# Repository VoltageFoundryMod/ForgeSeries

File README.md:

<div align="center">

# ForgeSeries

**One open-source Eurorack platform. Many modules. You choose which one it is at
power-on — and the same firmware also runs inside VCV Rack.**

[The modules](#the-modules) ·
[Get one running](#get-one-running) ·
[The board](#the-board) ·
[Building from source](#building) ·
[How it fits together](#how-it-fits-together)

[Website & manuals](https://vfmod.com) ·
[Hardware repo](https://github.com/VoltageFoundryMod/ForgeSeries-Hardware) ·
[Firmware releases](https://github.com/VoltageFoundryMod/ForgeSeries/releases) ·
[Support on Patreon](https://patreon.com/carlosedp)

</div>

---

## What this is

ForgeSeries is a family of 6HP Eurorack modules from **Voltage Foundry Modular**
that all share a single board: a Seeed XIAO RP2040, a 128×64 OLED, one encoder,
3 CV inputs and 4 outputs. What makes the board a clock generator or a quantizer
is nothing but firmware.

This repository holds all of it:

- **The firmware** — one image (`src/`) that contains _every_ module. Hold
  the encoder at power-on to pick which one boots; the choice persists.
- **The VCV Rack plugin** — not a reimplementation. The actual firmware runs
  inside Rack against a hardware shim, with the OLED emulated pixel for pixel,
  so a patch behaves the same on the metal and on the screen.
- **The shared core** — board bring-up, CV calibration, storage, display and
  menu plumbing that every module builds on.

Schematics, PCB and panel files are open too, in the separate
[ForgeSeries-Hardware](https://github.com/VoltageFoundryMod/ForgeSeries-Hardware)
repository.

## The modules

|                                                                                 | Module                                    | What it does                                                                                                                                                                                                      | Docs                                                                                                                                                                                      |
| ------------------------------------------------------------------------------- | ----------------------------------------- | ----------------------------------------------------------------------------------------------------------------------------------------------------------------------------------------------------------------- | ----------------------------------------------------------------------------------------------------------------------------------------------------------------------------------------- |
|    | **ClockForge**<br><sub>`apps/clk`</sub>   | Clock generator and modulation source. Four outputs with individual multiply/divide, waveforms, envelopes, Euclidean rhythms, swing, phase, probability, cross-operations and loops. Tap tempo and external sync. | [Overview](apps/clk/Readme.md) · [Manual](apps/clk/Manual.md) · [VCV port](apps/clk/docs/VCVRack_Plugin.md) · [ModularGrid](https://modulargrid.net/e/voltage-foundry-modular-clockforge) |
|      | **NoteForge**<br><sub>`apps/dq`</sub>     | Dual quantizer. Two independent channels, each with its own editable 12-note scale mask, octave shift, glide, sample & hold and a gate/envelope output.                                                           | [Overview](apps/dq/Readme.md) · [Manual](apps/dq/Manual.md) · [VCV port](apps/dq/docs/VCVRack_Plugin.md) · [ModularGrid](https://modulargrid.net/e/voltage-foundry-modular-noteforge)     |
|  | **GravityForge**<br><sub>`apps/gen`</sub> | Physics-based generative sequencer. Balls fall inside two rotating containers and ring scale-tuned pegs; a proximity control slides the two from independent sequencers into one entangled instrument.            | [Overview](apps/gen/Readme.md) · [Manual](apps/gen/Manual.md) · [Design notes](apps/gen/docs/Design.md) · [ModularGrid](https://modulargrid.net/e/voltage-foundry-modular-gravityforge)   |
|     | **ForgeView**<br><sub>`apps/scp`</sub>    | Oscilloscope and analysis. Dual-trace and single-trace scope, triggered capture, spectrum analyzer, X-Y display and a tuner — with buffered pass-through so it can sit mid-patch.                                 | [Overview](apps/scp/Readme.md) · [Manual](apps/scp/Manual.md) · [VCV port](apps/scp/docs/VCVRack_Plugin.md) · [ModularGrid](https://modulargrid.net/e/voltage-foundry-modular-forgeview)  |
|    | **ChaosForge**<br><sub>`apps/att`</sub>   | Dual chaotic-attractor modulation source. Twelve strange attractors; each generator sends two of its three state variables to a pair of jacks, and a couple control takes the two from unrelated to locked.       | [Overview](apps/att/Readme.md) · [Manual](apps/att/Manual.md) · [Design notes](apps/att/docs/Design.md) · [ModularGrid](https://modulargrid.net/e/voltage-foundry-modular-chaosforge)     |
|    | **WeaveForge**<br><sub>`apps/wea`</sub>   | Dual shift-register sequencer. Two Turing Machines side by side, and one WEAVE control that slides them from independent to chained into a single ring; four jacks assignable to notes, modulation, gates or triggers.                     | [Overview](apps/wea/Readme.md) · [Manual](apps/wea/Manual.md) · [Design notes](apps/wea/docs/Design.md)                                                                                                                                    |

Each **Manual** is the complete user guide — every menu page, screenshot,
calibration and wiring detail. Browsable versions with images live on
[vfmod.com](https://vfmod.com).

### Expanders

|                                                                                      | Module                                         | What it does                                                                                                                                                       | Docs                                                                                                                                                                     |
| ------------------------------------------------------------------------------------ | ---------------------------------------------- | ------------------------------------------------------------------------------------------------------------------------------------------------------------------ | ------------------------------------------------------------------------------------------------------------------------------------------------------------------------ |
|  | **Forge Expander 1**<br><sub>`apps/exp1`</sub> | 4 HP expander adding four outputs (**5**–**8**) and one CV input (**CV 3**) to a host module. Ribbon cable to the host's expansion header, powered from it.        | [Manual](apps/exp1/Manual.md) · [In ClockForge](apps/clk/Manual.md#expander) · [ModularGrid](https://modulargrid.net/e/voltage-foundry-modular-forge-expander-1)         |

The expander carries jacks and analog stages, not a microcontroller — what the
extra jacks do is decided by the host firmware, so each module can use it its own
way and one expander serves all of them. **ClockForge** is the first to support
it, turning its four outputs into eight and adding a third CV modulation source.
Its VCV Rack module and its panel are built as part of its host's plugin, which
is why the code lives under `apps/clk/` while the docs and artwork live in
`apps/exp1/`.

## Get one running

### On hardware

1. Download `ForgeSeries-<version>-unified.zip` from the [latest release](https://github.com/VoltageFoundryMod/ForgeSeries/releases) or a [dev build](https://github.com/VoltageFoundryMod/ForgeSeries/actions) from CI run's artifacts (enter one of the workflow runs and the artifacts are at the bottom) and unpack the `.uf2` inside it.
2. Hold the small **BOOT (B)** button on the XIAO while connecting USB-C. A
   drive named `RPI-RP2` appears. (The XIAO is socketed, so this can be done
   with it removed from the module.)
3. Copy the `.uf2` onto that drive. The module reboots into the new firmware.
4. **Hold the encoder at power-on** to choose a module. It boots straight into
   that one afterwards; to get back to the selector, either hold the encoder for
   two seconds while running or pick **BOOT MENU** on the module's SETTINGS page.
5. Run the two-point **calibration wizard** once: pick **CALIBRATE**,
   the last row of the boot menu. Calibration works for the board, so one
   run serves every module and it survives firmware updates.

#### Single-module images

`ForgeSeries-<version>-individual-modules.zip` on the same release holds one image per
module — `ClockForge`, `NoteForge`, `GravityForge`, `ForgeView`, `ChaosForge`,
`WeaveForge` —
for a build of
the hardware that is only ever going to be one of them. Flashing works exactly
as above, and everything else in this section still applies: the module boots
straight in, and holding the encoder at power-on (or **BOOT MENU** on its
SETTINGS page) opens the same screen with that one module and **CALIBRATE** on
it, which is how you reach the wizard.

They are the same shell and the same module sources as the unified image, just
linked with one module instead of all of them, so a given release behaves identically
either way. Presets and calibration live in the same files, so you can move
between the two images without losing either.

> **Never connect Eurorack power and USB-C at the same time.** The module takes
> either, not both.

### In VCV Rack

The plugin bundles every module under the **Voltage Foundry Modular** brand.
Until it lands in the VCV library, build it from source — see
[Building](#building) — or take the packaged `.vcvplugin` from the [latest release](https://github.com/VoltageFoundryMod/ForgeSeries/releases) or a [dev build](https://github.com/VoltageFoundryMod/ForgeSeries/actions) from CI run's artifacts (enter one of the workflow runs and the artifacts are at the bottom).

```sh
make vcv && make vcv-install   # build the bundle and install it into Rack
```

And drop the `.vcvrack` file into plugins in the VCVRack user folder. MacOS is `~/Library/Application Support/Rack2/`, Windows is `C:\Users\<username>\AppData\Local\Rack2\`, and Linux is `~/.local/share/Rack2/`.

The Rack build can accept 0–5 V (like the hardware), ±5 V or 0–10 V inputs, so
it is more forgiving than the board while behaving identically inside that
range.

## The board

Every ForgeSeries module is the same hardware:

|          |                                                                     |
| -------- | ------------------------------------------------------------------- |
| MCU      | Seeed XIAO RP2040 (dual core, 2 MB flash)                           |
| Display  | 128×64 SSD1306 OLED                                                 |
| Controls | one rotary encoder with push                                        |
| I/O      | 3 CV inputs, 4 outputs (12-bit MCP4728 DAC)                         |
| CV range | 0–5 V in and out (a ±5 V revision builds with `-DFORGE_CV_BIPOLAR`) |
| Size     | 6 HP, 40 mm deep                                                    |
| Power    | 12 V or 5 V, jumper selectable · ~60 mA                             |

Because the hardware is identical across modules, one board plus one firmware
flash gets you any of them — and a new module is a new firmware, not a new PCB.

The board also carries an expansion header, which
[Forge Expander 1](#expanders) uses to add a second DAC and a fourth input —
8 outputs and 4 inputs in total, on modules whose firmware supports it.

## Repository layout

```text
platformio.ini  the firmware project — the repo root IS the PlatformIO project
src/            the shell. The only firmware built for the board
core/      the board, and everything every module shares
apps/
  clk/     ClockForge    — clock generator / modulation source
  dq/      NoteForge     — dual quantizer
  gen/     GravityForge  — physics-based generative sequencer
  scp/     ForgeView     — oscilloscope / spectrum analyser
  att/     ChaosForge    — dual chaotic-attractor modulation source
  wea/     WeaveForge    — dual shift-register sequencer
  exp1/    Forge Exp 1   — expander docs + artwork; no firmware, no code
vcv/       the consolidated VCV Rack plugin (all modules, one binary)
vcvlib/    shared VCV Rack layer (Arduino shim, ForgeModule, IEngine, widgets)
tools/     env.ps1 — optional PATH helper for Windows
```

A module runs on two hosts — the shell (hardware firmware) and VCV Rack — and
its code lives in one place per host:

```text
apps/gen/
  src/gen_app.cpp   the module as the shell sees it (forge::IApp)
  src/gen_app.hpp   its factory — the only thing the shell includes
  lib/              the module's own headers, including engine.hpp
  vcv-plugin/       the same module as a standalone Rack plugin
  test/             native unit tests (googletest + ArduinoFake)
  platformio.ini    those tests only — there is no per-module firmware
```

`lib/engine.hpp` is the piece that keeps the two honest: the module's
per-iteration engine step lives there and both hosts include it, rather than
each carrying a copy. That duplication is how GravityForge's Rack port silently
lost its LOOP▸NAP muting.

## Building

Prerequisites: [PlatformIO](https://platformio.org/) for the firmware, and the
[VCV Rack SDK](https://vcvrack.com/manual/Building) for the plugins (expected at
`../Rack-SDK`, override with `RACK_DIR=`).

```sh
make                # the firmware (unified image, every module)
make upload         # build + flash
make upload-monitor # ...and open the serial monitor
make modules        # the single-module images, one per module
make fw-clk         # one of them  (== pio run -e xiao_clk)
make fw-upload-clk  # ...and flash it
make test           # native unit tests for every module
make vcv            # the consolidated Rack plugin
make vcv-install    # ...and install it into Rack's user directory
make vcv-dist       # package it as a .vcvplugin
make plugins        # every standalone per-module Rack plugin
make clk            # one module's standalone plugin, installed into Rack
make everything     # every firmware image + all standalone plugins
```

**Run `make everything` before committing.** It is the only thing that builds
both hosts. PlatformIO does not compile `vcv-plugin/`, so a green firmware build
says nothing about the Rack ports — and every bug found while this structure was
being built was caught by building all targets and missed by building one.

> **Do not leave both plugin flavours installed in Rack.** The standalone
> plugins have their own slugs (`ClockForge`, `NoteForge`, …) and the
> consolidated one is `VoltageFoundryMod`, so Rack happily loads all of them and
> every module shows up twice in the browser. Delete the standalone ones from
> Rack's plugin directory before installing the consolidated build
> (`make -C vcv print-plugins-dir` prints where that is).

Standalone plugins can also be built directly. Both paths are `?=` defaults:

```sh
cd apps/gen/vcv-plugin && make          # RACK_DIR ?= ../../../../Rack-SDK
make RACK_DIR=/path/to/Rack-SDK         # out-of-tree SDK
```

`FORGEVCV` defaults to `../../../vcvlib` (in-repo). It no longer needs a sibling
`ForgeSeries-VCVLib` checkout.

[CI](.github/workflows/CI.yaml) drives these same entry points, so what it
checks and what you run locally cannot drift apart: unit tests and the unified
image, the VCV engine isolation tests, and both plugin flavours.

### Windows toolchain

Everything builds from PowerShell — an msys2 _shell_ is not required. Rack's
`plugin.mk` shells out to POSIX tools, but GNU make picks up msys2's `sh.exe` as
SHELL once it is on PATH, so PowerShell only has to be the parent shell.

```powershell
. .\tools\env.ps1   # puts the three toolchain dirs on PATH, reports what it found
make everything
```

The plugin compiler must be **mingw64 g++** — the Rack SDK for Windows is
mingw-w64 built and MSVC will not link against it. `jq` is needed too, since
`plugin.mk` uses it to read `SLUG` out of `plugin.json`:

```
pacman -S --needed make mingw-w64-x86_64-gcc mingw-w64-x86_64-jq
```

The Makefile checks for all three before building plugins and says exactly what
is missing, rather than letting it surface as plugin.mk's "SLUG could not be
found in manifest". The check runs only for the plugin goals — the firmware
needs PlatformIO alone and builds without msys2 installed.

Point `MSYS` elsewhere if needed: `make MSYS=D:/msys64 plugins`.

---

# How it fits together

The rest of this document is for people working on the code. Start here if you
are adding a module, touching `core/`, or wondering why the include order in a
module TU looks the way it does.

## What belongs in `core/`

Every ForgeSeries module is the _same board_: XIAO RP2040, SSD1306 on Wire,
MCP4728 on Wire1, one encoder, 3 in / 4 out. Anything that follows from that is
shared:

|                                                                       |                                                              |
| --------------------------------------------------------------------- | ------------------------------------------------------------ |
| `boardPinouts.hpp`                                                    | wiring, converter resolution (`MAXDAC`/`MAXADC`)             |
| `boardIO.hpp`                                                         | I2C bring-up, DAC writes + output calibration                |
| `cvInput.hpp`                                                         | CV acquisition, calibration, range adapters                  |
| `calibrationData.hpp` `calibration.hpp`                               | the blob, and the wizard that fills it                       |
| `fsStore.hpp` `appStorage.hpp`                                        | LittleFS storage; presets and calibration                    |
| `shellObjects.hpp`                                                    | the board-owned `display` / `displayMgr` / `encoder` / `cal` |
| `displayManager.hpp` `menuDisplay.hpp` `appDisplay.hpp` `splash.hpp`  | UI plumbing                                                  |
| `encoder.hpp` `encoderAccel.hpp` `encoderMenu.hpp`                    | encoder, acceleration, menu driver                           |
| `envelope.hpp` `scales.hpp` `quantizer.hpp` `utils.hpp` `metrics.hpp` | shared DSP/theory                                            |
| `clockSource.hpp`                                                     | internal BPM, external clock at IN 1, the changeover         |
| `IApp.hpp`                                                            | the shell↔app contract                                       |

What stays in a module's `lib/` is genuinely its own: menu definitions, preset
schema, `engine.hpp`, and the DSP that makes it that module.

ClockForge's quantizer is deliberately not shared: it is a separate
implementation reached through `Output` rather than a channel, so folding it in
would be a port rather than a merge.

**Neither is ClockForge's clock**, for the same reason and with more at stake.
`core/clockSource.hpp` is a passed-in-time value object — nothing in it calls
`micros()`, which is what makes it host-testable and the Rack ports
deterministic. `apps/clk/lib/clockEngine.hpp` is a 960-PPQN hardware-timer ISR
with file-scope `BPM` and `tickCounter` globals driving that whole module from
the interrupt. They share a word, not an architecture. `clockSource.hpp` was
lifted out of GravityForge when WeaveForge needed the same internal/external
changeover, and GravityForge holds one as a member rather than having been
rewritten around it — its `Clock` still owns the quantize grid, SPACE and the
spin rates, and its 21 clock tests were the guard that the lift changed nothing.

Two rules govern anything living here, and both have bitten:

**Anything `core/` defines must be `inline`** (C++17 inline variables included).
The unified image links the shell plus one TU per module; without it you get a
duplicate symbol, or worse a file-scope `static` gives each TU a private copy of
what should be shared hardware state.

**`core/` must never include an app header.** `boardIO.hpp` once included the
module-level `pinouts.hpp` and made `core/` unbuildable without a module on the
include path. Where a shared header genuinely needs data the caller owns, it
requires the caller to have defined it rather than reaching for it — the way
`calibration.hpp` takes `SaveCalibration()` from the shell.

## CV, and the ±5 V hardware

Readings are **normalised floats**: `1.0` is +5 V at the jack on every hardware
revision. Not counts — a count means nothing without also knowing `MAXADC` and
the polarity convention, and presets store values derived from these.

```
unipolar (0..+5 V)   CvRead() ->  0.0 .. 1.0
bipolar  (-5..+5 V)  CvRead() -> -1.0 .. 1.0,  0 V == 0.0
```

Build for the ±5 V revision with `-DFORGE_CV_BIPOLAR`. Apps must read through
the adapters rather than open-coding a mapping, because which one is the
identity swaps when the flag flips:

|                | unipolar | bipolar   |
| -------------- | -------- | --------- |
| `CvUni` → 0..1 | identity | `(v+1)/2` |
| `CvBi` → -1..1 | `v*2-1`  | identity  |

Pitch is **not** normalised — `CvSemitones()` returns 1 V/oct semitones, and DAC
output stays in counts, scaled at the write. Three domains, three units.

0 V is C0 on both revisions, so the bipolar jack keeps the same five-octave
span. Moving C0 to -3 V for eight octaves is a future opt-in menu setting, not
something implied by the hardware.

## The unified firmware

`src/` is the shell and nothing else. It owns the board — one `display`,
one `encoder`, one `cal` — brings the hardware up, mounts the filesystem, runs
the module selector, then drives exactly one module through `forge::IApp`
(`Begin`/`Tick0`/`Tick1` + encoder events). The core split is the one every
firmware already used: Core 0 does ADC/DAC/encoder, Core 1 renders.

**Using it.** Hold the encoder at power-on to choose a module; the choice
persists, so it boots straight into it afterwards. Two ways back to the
selector: hold the encoder for two seconds while running, or pick **BOOT MENU**
on the module's SETTINGS page. Either way the switch reboots rather than
unwinding in place — a running module owns interrupts, a hardware timer and
Core 1 work — so `End()` is called first and a flag survives the reset.

The selector's last row is **CALIBRATE**, and it is the only way into the
wizard. Calibration measures the board's analog front and back ends, not
anything module-specific, so it belongs to the shell — and it has to run with
Core 1 parked and no module started, which is only true on this screen. It
writes `/cal.bin` and reboots back to the selector.

The held-encoder check happens before any module code runs, so a module that
hangs in its own `Begin()` can still be escaped by holding the encoder and
power-cycling.

**Single-module images.** `env:xiao_clk` and its three siblings build the same
shell with one module linked in — for hardware that is only ever going to be
that module. `make modules`, or `make fw-clk` for one.

The shell is not modified for this and neither is any module. The environment
passes `-DFORGE_ONLY_APP=<Factory>`, and the single `#ifdef` in `kApps[]` builds
an array of one from it. Everything above still holds with `kAppCount == 1`: the
module boots straight in, the selector lists it and **CALIBRATE**, and
`FORGE_UNIFIED` stays defined so **BOOT MENU** is still on the module's SETTINGS
page. Stripping the selector out instead is what would have cost something — it
is the only entry point to the wizard, so removing it means either an `#ifdef`
axis through every module's `menuHandlers.hpp` or no field calibration.

Naming the factory rather than setting a per-module flag is what keeps that to
one `#ifdef`: it covers every module, present and future, so adding one is still
just an include and an array entry. The `<app>_app.hpp` includes stay
unconditional even in a single-module image, because they only _declare_ a
factory — an unused declaration is not a link reference, so nothing is paid for
the three that are not there.

The array is written out rather than having each module TU register itself at
static-init time, because `/boot` stores an _index_ into it and static-init order
across translation units is unspecified — self-registration would let link order
decide what index 2 means.

**Storage** is LittleFS, not the emulated EEPROM. That sector is a single 4096
bytes and its `begin()` clamps silently — which is how ClockForge shipped with
permanently broken calibration and three dead preset slots. Several modules could
never have shared it.

```
/cal.bin      CalibrationData, shared by every module
/boot         which module to start, and a return-to-menu flag
/<app><n>.pre one preset slot
```

One file per slot, so a write is a whole-file atomic replace and the slot count
is no longer capped by a sector. Every write goes via a temp file and a rename;
every read checks a magic and an exact length, and anything that fails reads as
absent so the caller falls back to defaults.

**Namespaces.** Each module TU wraps itself in `namespace forge::<app>`, which
is what lets several firmwares share one binary — they all define `menuMode`,
`switchState`, `param` and friends at file scope.

> **Include order in a module TU is load-bearing.** Standard library,
> third-party and `core/` headers go at _global_ scope first, so their guards
> are already satisfied; only then the module's own headers, inside the
> namespace. Miss one — `<cstring>`, say — and libstdc++ lands inside
> `forge::<app>`, producing hundreds of errors in `stringfwd.h` that never name
> the file responsible. The blocks are bracketed with `clang-format off/on`
> because an editor that sorts includes will break this silently. See the header
> comment in `apps/scp/src/scp_app.cpp`.

A few `core/` headers are included _late_, after the module's state exists,
because they close over it: `engine.hpp` (the module's globals),
`appDisplay.hpp` (`HandleOutputs`, the display flags) and `encoderMenu.hpp`
(the five hooks). That is the price of sharing code that calls back into
per-module state.

## Image size, and how it scales

The root `platformio.ini` pulls each module TU in through `build_src_filter`, so
sources stay with their module rather than being copied. Only each module's
`src/` is on the include path: it holds nothing but the uniquely-named
`<app>_app.hpp`, so unlike putting the `lib/` dirs there it cannot shadow a
sibling's header. (It once did — GravityForge resolved `quantizer.hpp` to
NoteForge's copy purely because `dq` came first in the include path.)

Current size, every module in one image:

|         | RAM            | Flash           |
| ------- | -------------- | --------------- |
| unified | 31108 (11.9 %) | 280508 (15.3 %) |

Flash is measured against 1830912 bytes — 256 KB of the 2 MB part is reserved
for the LittleFS region, and that size must stay fixed across releases or the
region moves and stored files are lost.

Only one module _runs_ at a time, but all of them are _linked_, so static RAM is
the sum of every module's state rather than the maximum. That sounds worse than
it is: most of a module's apparent footprint is the Arduino/TinyUSB baseline,
which is paid once. What a module actually adds is its own translation unit's
`data+bss`:

| module | RAM added | flash added |
| ------ | --------- | ----------- |
| clk    | ~7 KB     | ~46 KB      |
| gen    | ~1.9 KB   | ~28 KB      |
| scp    | ~1.2 KB   | ~14 KB      |
| dq     | ~0.7 KB   | ~19 KB      |
| wea    | ~0.5 KB   | ~17 KB      |
| shell  | ~0.2 KB   | ~2 KB       |

Baseline is ~17.8 KB. Six modules is ~12 % of RAM, so ten ClockForge-weight
ones would be ~34 % and ten typical ones ~15 %. Flash is looser still.

WeaveForge is the cheapest so far and shows where the cost actually is: its
engine is two `uint16_t` and a few dozen bytes of parameters, and essentially all
of its ~17 KB of flash is menu, render and preset code — the plumbing every
module pays, not the DSP that makes it that module.

ClockForge is the outlier at 10× NoteForge — if RAM ever gets tight, that one
module is the lever, not the module count.

If it did get tight, the escape hatch is half-built: each module's
`vcv-plugin/src/engine/engine_state.def` already enumerates every mutable global
it owns, because the Rack port needs per-instance state. The same X-macro could
size a shared arena and make RAM `max(module)` rather than `sum(modules)`. Not
needed at five, probably not at ten — but the enumeration exists, and it is
worth keeping accurate as modules are added, since only the Rack build catches a
stale entry.

## History

This repo was assembled from five separate repositories with `git subtree`, so
all 311 original commits are preserved and reachable.

Because the files moved into `apps/<app>/`, git's default history simplification
hides pre-import commits. To see them, ask for the **old** path with
`--full-history`:

```sh
git log --full-history -- lib/storage.hpp        # CLK's pre-import history
git log --full-history -- include/forgevcv/      # VCVLib's
```

Post-import history uses the new paths as normal.

The original repositories remain untouched on disk and on GitHub. They are the
authoritative record for anything predating the import.

---

## Contributing & support

Issues and pull requests are welcome on the
[GitHub repository](https://github.com/VoltageFoundryMod/ForgeSeries). If a
module misbehaves, its **Manual** has a troubleshooting section worth checking
first.

See [CONTRIBUTING.md](CONTRIBUTING.md) before opening a PR. Commits need a
`Signed-off-by` line (`git commit -s`) certifying the
[DCO](DCO); contributions are under GPL-3.0-or-later, like the rest of the code.
Panel and brand assets are not open to contribution — see
[LICENSE-ASSETS.md](LICENSE-ASSETS.md).

If these modules are useful to you, development is supported on
[Patreon](https://patreon.com/carlosedp) and
[GitHub Sponsors](https://github.com/sponsors/carlosedp).

## License

Two licences, covering two different things.

**The code — [GPL-3.0-or-later](LICENSE).** All of it: firmware, the VCV Rack
port, the shared core, the tooling. Fork it, study it, build on it, ship your
own version — provided your version is free software too. That is the whole
point: the ideas here should be reusable, and a proprietary product should not
be able to quietly absorb them.

**The brand — [LICENSE-ASSETS.md](LICENSE-ASSETS.md).** Panel designs, graphics,
the logo, and the names "Voltage Foundry Modular", "ForgeSeries" and the module
names are copyright and not covered by the GPL. You may build and run the
software with the artwork in place, and distribute modified versions that are
clearly marked as unofficial; you may not manufacture hardware wearing these
panels or ship something that looks like it came from us. Fork the code, put
your own face on it.

Hardware design files carry their own license in the
[hardware repository](https://github.com/VoltageFoundryMod/ForgeSeries-Hardware).

<div align="center">
<sub>Voltage Foundry Modular — open-source Eurorack, forged in code and copper.</sub>
</div>

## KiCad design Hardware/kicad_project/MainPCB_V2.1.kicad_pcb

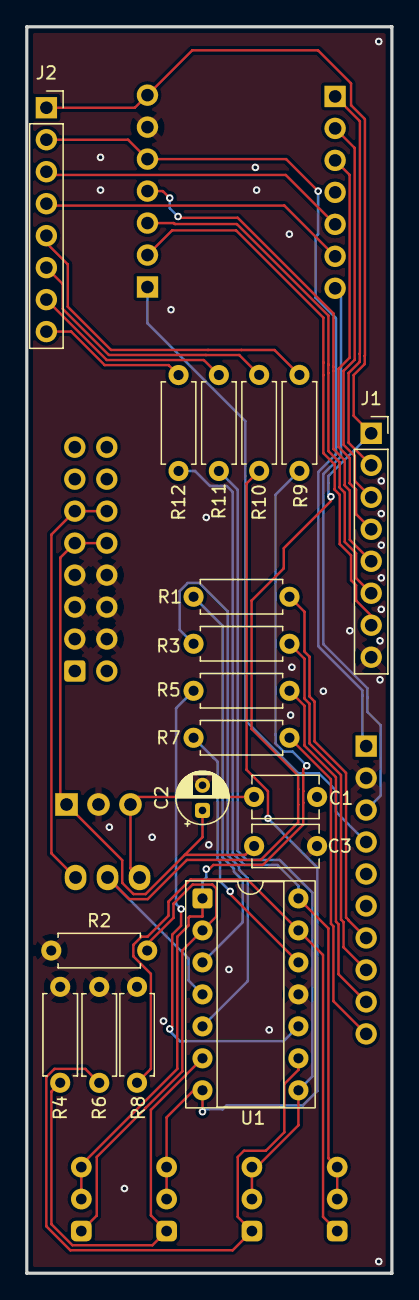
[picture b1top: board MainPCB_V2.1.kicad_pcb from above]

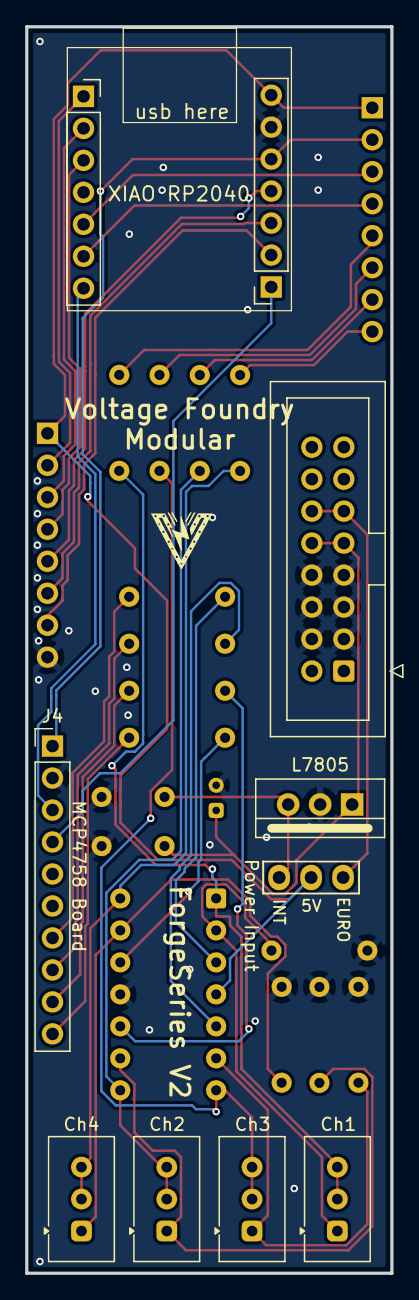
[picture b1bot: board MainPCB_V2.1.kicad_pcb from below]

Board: 2 copper layers, 29.0 x 99.0 mm, 28 parts (10 on the bottom side), 36 nets.

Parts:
C1, C3: 100n; C_Disc_D5.1mm_W3.2mm_P5.00mm
C2: 10u; CP_Radial_D4.0mm_P2.00mm
Ch1, Ch2, Ch3, Ch4: 5k; Potentiometer_Vishay_T93YA_Vertical
J1, J2: Conn_01x08; PinSocket_1x08_P2.54mm_Vertical
J3: Power Input; Pins_1x03_2.54mm_TH
J4: MCP4758 Board; PinHeader_1x10_P2.54mm_Vertical
J5: POWER IN; IDC-Header_2x08_P2.54mm_Vertical
J6, J7: Conn_01x07; PinSocket_1x07_P2.54mm_Vertical
R1, R3, R5, R7: 10k; R_Axial_DIN0207_L6.3mm_D2.5mm_P7.62mm_Horizontal
R2, R4, R6, R8: 6k8; R_Axial_DIN0207_L6.3mm_D2.5mm_P7.62mm_Horizontal
R9, R10, R11, R12: 470; R_Axial_DIN0207_L6.3mm_D2.5mm_P7.62mm_Horizontal
U1: MCP6004; DIP-14_W7.62mm_Socket
U2: L7805; TO-220-3_Vertical

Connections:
5V: J1.1, J2.1, J3.2, J7.7, U1.4 (V+)
5V_IN: J3.3, J5.11, J5.12
5V_REG: C1.1, J3.1, U2.3 (OUT)
12V: C2.1, C3.1, J5.9, J5.10, U2.1 (IN)
ARD_3: J2.2, J4.1, J7.5
ENC_1: J1.6, J7.3
ENC_2: J1.7, J7.2
ENC_SW: J1.5, J7.4
GND: C1.2, C2.2, C3.2, J1.8, J4.2, J5.3, J5.4, J5.5, J5.6, J5.7, J5.8, J7.6, R2.1, R4.1, R6.1, R8.1, U1.11 (V-), U2.2 (GND)
IN_1: J1.2, J6.1
IN_2: J1.3, J6.2
IN_3: J1.4, J6.3
unnamed: Ch1.2, Ch1.3, R9.1, U1.1
unnamed: Ch3.2, Ch3.3, R10.1, U1.7
unnamed: Ch2.2, Ch2.3, R11.1, U1.8
unnamed: Ch4.2, Ch4.3, R12.1, U1.14
unnamed: R1.2, U1.3 (+)
unnamed: Ch1.1, R2.2, U1.2 (-)
unnamed: R3.2, U1.5 (+)
unnamed: Ch3.1, R4.2, U1.6 (-)
unnamed: R5.2, U1.10 (+)
unnamed: Ch2.1, R6.2, U1.9 (-)
unnamed: R7.2, U1.12 (+)
unnamed: Ch4.1, R8.2, U1.13 (-)
O1_CON: J2.5, R9.2
O2_CON: J2.6, R10.2
O3_CON: J2.7, R11.2
O4_CON: J2.8, R12.2
O_1: J4.7, R1.1
O_2: J4.8, R3.1
O_3: J4.9, R5.1
O_4: J4.10, R7.1
SCL: J2.4, J6.6
SCL2: J4.3, J6.7
SDA: J2.3, J6.5
SDA2: J4.4, J7.1

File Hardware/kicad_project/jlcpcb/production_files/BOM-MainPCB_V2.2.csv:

Comment,Designator,Footprint,LCSC,Quantity
Conn_01x08,J2,PinSocket_1x08_P2.54mm_Vertical,,1
Conn_01x08,J1,PinSocket_1x08_P2.54mm_Vertical,,1
Power In,J3,Pins_1x03_2.54mm_TH,,1
MCP4758 Board,J4,PinHeader_1x10_P2.54mm_Vertical,,1
POWER IN,J5,PinHeader_2x08_P2.54mm_Vertical,,1
Conn_01x07,J6,PinSocket_1x07_P2.54mm_Vertical,,1
Conn_01x07,J7,PinSocket_1x07_P2.54mm_Vertical,,1
L7805,U2,TO-220-3_Vertical,,1
10k,R3,R_Axial_DIN0207_L6.3mm_D2.5mm_P7.62mm_Horizontal,,1
6k8,R4,R_Axial_DIN0207_L6.3mm_D2.5mm_P7.62mm_Horizontal,,1
470,R9,R_Axial_DIN0207_L6.3mm_D2.5mm_P7.62mm_Horizontal,,1
10k,R1,R_Axial_DIN0207_L6.3mm_D2.5mm_P7.62mm_Horizontal,,1
6k8,R8,R_Axial_DIN0207_L6.3mm_D2.5mm_P7.62mm_Horizontal,,1
10u,C2,CP_Radial_D4.0mm_P2.00mm,,1
470,R11,R_Axial_DIN0207_L6.3mm_D2.5mm_P7.62mm_Horizontal,,1
10k,R5,R_Axial_DIN0207_L6.3mm_D2.5mm_P7.62mm_Horizontal,,1
10k,R7,R_Axial_DIN0207_L6.3mm_D2.5mm_P7.62mm_Horizontal,,1
100n,C3,C_Disc_D5.1mm_W3.2mm_P5.00mm,,1
6k8,R6,R_Axial_DIN0207_L6.3mm_D2.5mm_P7.62mm_Horizontal,,1
MCP6004,U1,DIP-14_W7.62mm_Socket,,1
100n,C1,C_Disc_D5.1mm_W3.2mm_P5.00mm,,1
470,R10,R_Axial_DIN0207_L6.3mm_D2.5mm_P7.62mm_Horizontal,,1
470,R12,R_Axial_DIN0207_L6.3mm_D2.5mm_P7.62mm_Horizontal,,1
6k8,R2,R_Axial_DIN0207_L6.3mm_D2.5mm_P7.62mm_Horizontal,,1
5k,Ch3,Potentiometer_Vishay_T93YA_Vertical,,1
5k,Ch1,Potentiometer_Vishay_T93YA_Vertical,,1
5k,Ch2,Potentiometer_Vishay_T93YA_Vertical,,1
5k,Ch4,Potentiometer_Vishay_T93YA_Vertical,,1

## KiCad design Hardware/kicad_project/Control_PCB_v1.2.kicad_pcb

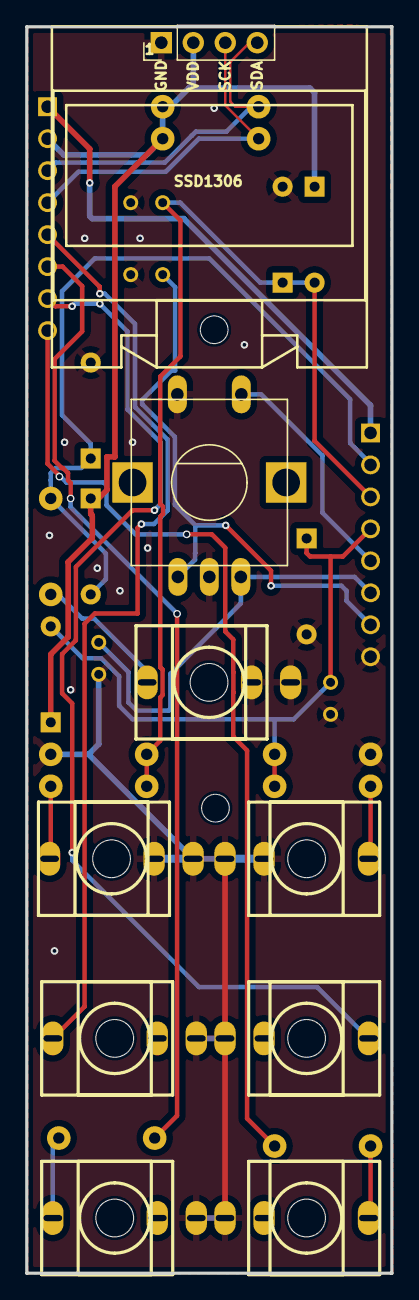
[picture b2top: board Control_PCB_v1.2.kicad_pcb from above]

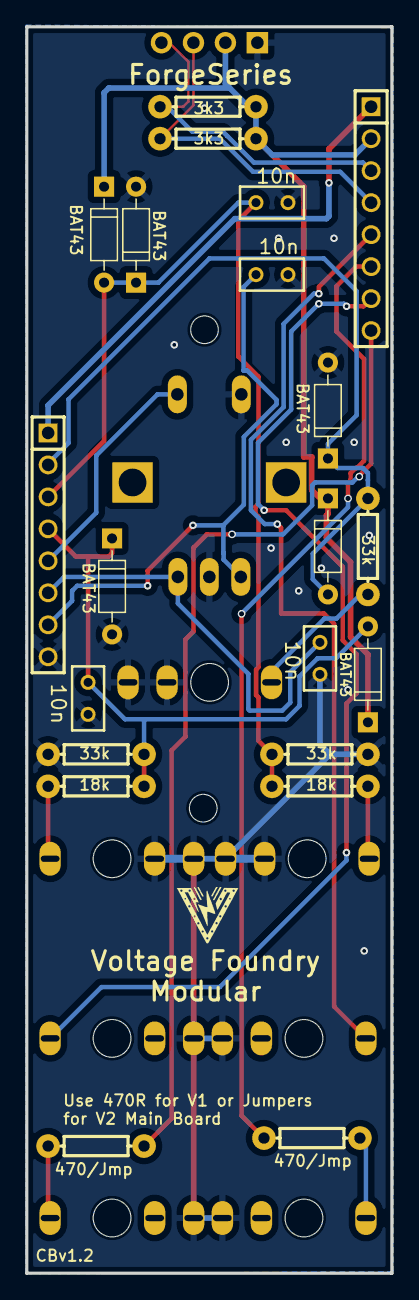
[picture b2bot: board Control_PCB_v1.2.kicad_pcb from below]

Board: 2 copper layers, 29.0 x 99.0 mm, 29 parts (6 on the bottom side), 20 nets.

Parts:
1: ALPS_ENCODER+PUSHSWITCHNORMAL; ENCODER+SWITCH
C7, C8, C9, C10: 10n; RAD-0.1
D1, D2, D3, D4, D5, D6: BAT43; D_DO-35_SOD27_P7.62MM_HORIZONTAL
H1, H2: Header-Male-2.54_1x8; HDR-TH_8P-P2.54-V-M
J1: O4; THONKICONN_1
J2: IN3; THONKICONN_1
J3: O1; THONKICONN_1
J4: IN1; THONKICONN_1
J5: IN2; THONKICONN_1
J6: O2; THONKICONN_1
J7: O3; THONKICONN_1
R13, R20: 470/Jmp; R_AXIAL-0.3
R14, R19: 18k; R_AXIAL-0.3
R15, R18, R21: 33k; R_AXIAL-0.3
R16, R17: 3k3; R_AXIAL-0.3

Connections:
5V: H1.1, H2.1
ARD_3: D1.1, D3.1, D4.1, H2.2, R16.1, R17.1
ENC_1: 1.B, C8.2, H1.6
ENC_2: 1.A, C9.1, H1.7
ENC_SW: 1.E, H1.5
GND: 1.C, 1.D, C7.1, C8.1, C9.2, C10.1, D2.2, D5.2, D6.2, H1.8, J1.1, J2.1, J2.2, J3.1, J4.1, J4.2, J5.1, J5.2, J6.1, J7.1, R15.2, R21.2
IN_1: D3.2, D5.1, H1.2, R18.1
IN_2: C10.2, D4.2, D6.1, H1.3, R19.1, R21.1
IN_3: C7.2, D1.2, D2.1, H1.4, R14.1, R15.1
J1_3: J1.3, R13.2
J5_3: J5.3, R19.2
J6_3: J6.3, R20.2
O1_CON: H2.5, J3.3
O2_CON: H2.6, R20.1
O3_CON: H2.7, J7.3
O4_CON: H2.8, R13.1
R14_2: J2.3, R14.2
R18_2: J4.3, R18.2
SCL: H2.4, R17.2
SDA: H2.3, R16.2

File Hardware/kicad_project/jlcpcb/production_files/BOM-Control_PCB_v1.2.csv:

Comment,Designator,Footprint,LCSC,Quantity
18k,R14,R_AXIAL-0.3,,1
IN3,J2,THONKICONN_1,,1
33k,R15,R_AXIAL-0.3,,1
18k,R19,R_AXIAL-0.3,,1
33k,R21,R_AXIAL-0.3,,1
470/Jmp,R13,R_AXIAL-0.3,,1
470/Jmp,R20,R_AXIAL-0.3,,1
BAT43,D1,D_DO-35_SOD27_P7.62MM_HORIZONTAL,,1
33k,R18,R_AXIAL-0.3,,1
3k3,R16,R_AXIAL-0.3,,1
BAT43,D6,D_DO-35_SOD27_P7.62MM_HORIZONTAL,,1
BAT43,D4,D_DO-35_SOD27_P7.62MM_HORIZONTAL,,1
ALPS_ENCODER+PUSHSWITCHNORMAL,1,ENCODER+SWITCH,,1
O4,J1,THONKICONN_1,,1
O1,J3,THONKICONN_1,,1
IN1,J4,THONKICONN_1,,1
IN2,J5,THONKICONN_1,,1
O2,J6,THONKICONN_1,,1
O3,J7,THONKICONN_1,,1
3k3,R17,R_AXIAL-0.3,,1
10n,C7,RAD-0.1,,1
10n,C8,RAD-0.1,,1
10n,C9,RAD-0.1,,1
10n,C10,RAD-0.1,,1
BAT43,D2,D_DO-35_SOD27_P7.62MM_HORIZONTAL,,1
BAT43,D3,D_DO-35_SOD27_P7.62MM_HORIZONTAL,,1
BAT43,D5,D_DO-35_SOD27_P7.62MM_HORIZONTAL,,1
Header-Male-2.54_1x8,H1,HDR-TH_8P-P2.54-V-M,,1
Header-Male-2.54_1x8,H2,HDR-TH_8P-P2.54-V-M,,1

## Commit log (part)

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2025-03-24 Skip envelope multiplier for digital outs
2025-03-24 New calibration method using the menu and self-calibration
2025-03-24 Add calibration to quantizer firmware. Still not ideal
2025-03-25 Add multiple reads and threshold to calibration
2025-05-03 Add sample test files
2025-05-03 Add blank panel template file
2025-05-03 Do multiple reads on calibrate
2026-01-19 Implement metrics to improve performance and find how to solve timing issues
2026-01-19 Change file permissions for firmware scripts to ensure proper execution
2026-04-24 Add new PCB for ForgeSeries 2 based on RP2040
2026-04-24 Initial working version of ClockForge 2. Add support for MCP4728 DAC on RP2040 and improve display management
    - Implemented MCP4728 quad DAC functionality for RP2040 architecture.
    - Added DisplayManager class for non-blocking OLED display updates.
    - Enhanced load/save functionality with EEPROM emulation for RP2040.
    - Updated metrics tracking for memory usage across architectures.
    - Refactored output handling to accommodate new DAC structure.
    - Improved encoder handling with polling mechanism for RP2040.
2026-04-24 Cleanup files
2026-04-24 feat(rp2040): dual-core + dual-I2C architecture
    - Wire1 (GPIO0/1) for MCP4728 DAC on Core 0
    - Wire (GPIO6/7) for SSD1306 display on Core 1
    - Core 0: timer ISR, encoder, CV, DAC writes — never blocked
    - Core 1: display.display() via _displayFrameReady flag
    - Removes all mutex/deferral workarounds
2026-04-25 refactor(DAC): optimize DACWriteAll for faster multi-channel updates
2026-04-25 Refactor code structure for improved readability and maintainability
2026-04-25 fix: save/load display corruption and output dropout on RP2040
    - Replace direct display.display() calls from Core 0 with ShowTemporaryMessage()
    helper that uses _displayFrameReady to route through Core 1 (Wire owner)
    - Add _displayLocked flag to pause Core 1 GFX rendering during temporary messages
    - Replace re-entrant HandleIO() wait loop with HandleOutputs()-only loop so DAC
    output continues during save/load confirmation screen
    - Fix encoder inversion caused by re-entrant HandleEncoderClick()
2026-04-25 feat(clock): implement clock generation and BPM control in clockEngine.hpp moving from main
2026-04-25 refactor(cvInputs): move CV input handling to new cvInputs.hpp file
2026-04-25 refactor(storage): rename loadsave.hpp to storage.hpp and update references. Centralize logic into presetManager and leave platform implementation in storage
2026-04-27 Now the MCP4728 uses it's own I2C bus on separate pins
2026-04-27 Phase 13: move HandleDisplay/MenuHeader/MenuIndicator to lib/menuRender.hpp
2026-04-27 feat(encoder): add encoder class implementation and integrate into main feat(clock): implement SetTapTempo function for BPM control refactor(menu): replace manual menu item count with automatic MENU_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
2026-04-27 feat(calibration): implement hardware calibration wizard and integrate calibration data handling
2026-04-27 feat(clock): enhance external clock handling and display feedback
2026-04-27 feat(outputs): add display blink state management for output indicators
2026-04-27 feat(outputs): update divider management to include additional clock dividers and adjust user-selectable options
2026-04-28 fix: resolve AR envelope 0V drop and envelope UX improvements
    - Fix Wire1 clock from 1MHz to 400kHz (MCP4728 rated max): at 1MHz
    tLOW=500ns violated the 1300ns minimum, causing silent I2C data
    corruption where the DAC ACKed but misinterpreted channel values,
    outputting 0V during AttackHold. Software values were always correct.
    - Block divisor changes via encoder when output is AD/AR/ADSR type;
    'Env' label remains visible as read-only indicator (IsEnvelopeType())
2026-04-28 docs: update Readme with envelope and waveform details
2026-04-28 Refactor menu handling for waveform and level/offset settings
    - Updated menu groups and item descriptions for clarity.
    - Consolidated waveform settings for all outputs into a single group.
    - Added level and offset settings for all outputs in a new group.
    - Adjusted envelope output selection to wrap across all outputs.
    - Fixed menu item indices and display handling for CV input targets.
    - Enhanced display rendering logic to reflect new menu structure.
2026-04-28 fix: update quantizer output selection logic and reset initial index
2026-04-28 fix: ignore triggers when output is disabled in outputs generating envelopes
2026-04-28 fix: add probability gate to trigger handling in envelope generation
2026-04-28 feat: add screen timeout settings and update menu handling
2026-04-28 feat: add Hatchet2 and Hatchet4 waveform types
2026-04-28 fix: update menu item column positions and improve display handling
2026-04-28 fix: adjust MaxDACValue for linear output range and prevent waveform clipping
2026-04-30 refactor: remove loadsave.hpp as it was renamed storage.hpp
2026-04-30 feat: update BOM files for V1 and V2, remove obsolete GERBER files, and enhance README for clarity
2026-04-30 Reformat all files based on LLVM rules
2026-04-30 refactor: streamline RP2040 specific code and remove SAMD21 compatibility from the 2.x firmware
2026-04-30 feat: update library dependencies and enhance build flags for improved performance
2026-04-30 refactor: remove legacy MCP4728 address definition and clean up unused code in boardIO and pinouts
2026-04-30 refactor: reorganize includes and remove unused pulse state check in Output class
2026-04-30 refactor: replace hardcoded values with MAX_STEPS and MAXDAC for improved maintainability
2026-04-30 refactor: increase number of preset slots from 5 to 10 for enhanced user functionality
2026-04-30 chore: update version from 2.0 to 2.1 for release
2026-04-30 Cleanup reference docs
2026-05-04 New Clockforge and Noteforge panels and logos
2026-05-04 New Control and Main PCBs with screw holes and updated control board with new routing.
2026-05-04 Update and organize PCB files
2026-05-04 Improve display pulse tracking indication and quantization support
2026-05-04 Add external clock pulse confirmation to improve sync reliability
2026-06-25 Add agents file
2026-06-25 Add cross operations and improve quantizer
2026-06-25 feat: Add loop functionality and output inversion to firmware
    - Introduced new loop features in the output management, allowing periodic rewind of pattern generators and nap/wake gating.
    - Added support for output inversion, enabling polarity flipping at the final output stage.
    - Updated the menu rendering to include new loop settings and output inversion options.
    - Enhanced the LoadSaveParams structure to accommodate new loop and inversion fields, ensuring backward compatibility with existing presets.
    - Adjusted the random number generation to support deterministic behavior for loops and cross operations.
    - Refactored output handling to integrate new loop and inversion functionalities seaml
2026-06-25 fix: Correct typos and improve clarity in Readme.md
2026-06-26 Separate repos for hardware and firmware
2026-06-26 Move DQ firmware to own repository. Previous history at https://github.com/VoltageFoundryMod/ForgeSeries.
2026-06-26 Add link to open-source hardware schematics in README
2026-06-26 Move GEN firmware to own repository. Previous history at https://github.com/VoltageFoundryMod/ForgeSeries.
2026-06-26 fix: Update Readme.md to clarify open-source availability of hardware schematics and design files
2026-06-26 feat: Enhance CV passthrough behavior and enforce envelope output constraints
2026-06-26 feat: Remove Building-Developing.md and add Hardware Design documentation; update Readme.md and Improvements.md; introduce VCV Rack Plugin reference and developer guide
2026-06-26 Fix placement of xops and loop menus
2026-06-26 Add Arduino core shims for VCV Rack integration
    - Implemented Arduino.h to provide a subset of the Arduino API, including HostBridge for I/O management.
    - Created EEPROM.h for EEPROM emulation using a byte buffer, allowing data persistence via JSON.
    - Developed WString.h as a minimal string class backed by std::string for compatibility with Arduino string operations.
    - Added Wire.h to implement I2C communication, handling MCP4728 multi-write frames for DAC outputs.
    - Included glcdfont.h for a fixed-space bitmap font compatible with Adafruit_GFX.
    - Introduced timer.h for RP2040 hardware timer functionality, providing inert stubs for hosted engine use.
2026-06-26 feat: Add VCV Plugin build and clean tasks to tasks.json
2026-06-26 fix: Update VCV Plugin task labels and move RACK SDK path to Makefile
2026-06-26 Disable workflow until we have proper tests for this fw
2026-06-26 feat: Enhance EncoderKnob appearance with detailed rim and body styling
2026-06-26 Add images to manual
2026-06-26 Add texture to module panel
